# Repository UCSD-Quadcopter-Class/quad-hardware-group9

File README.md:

# CSE 190 - QUAD-HARDWARE

This repo stores all of the files used during the creation of the quadcopter's
hardware design portion of the lab. The main schematic for the quadcopter is
`./quadcopter.sch`. The board file is `./quadcopter.brd`. The CAM files for the
board are in the file `./CAM/Group9-cam.zip`. Routing should be completed and
inspection is in progress.

## What do the Directories Contain?

### `./lbr`

Contains all of the library files used in EAGLE to create the schematic.

### `./datasheets`

Contains all of the datasheets or reference pages for the parts used in the 
quadcopter board.

### `./reference_sch`

Contains the shematics that were used as a reference while creating the 
quadcopter schematic.

### `./design_reviews`

Should contain all of the files that were created during a design review check.

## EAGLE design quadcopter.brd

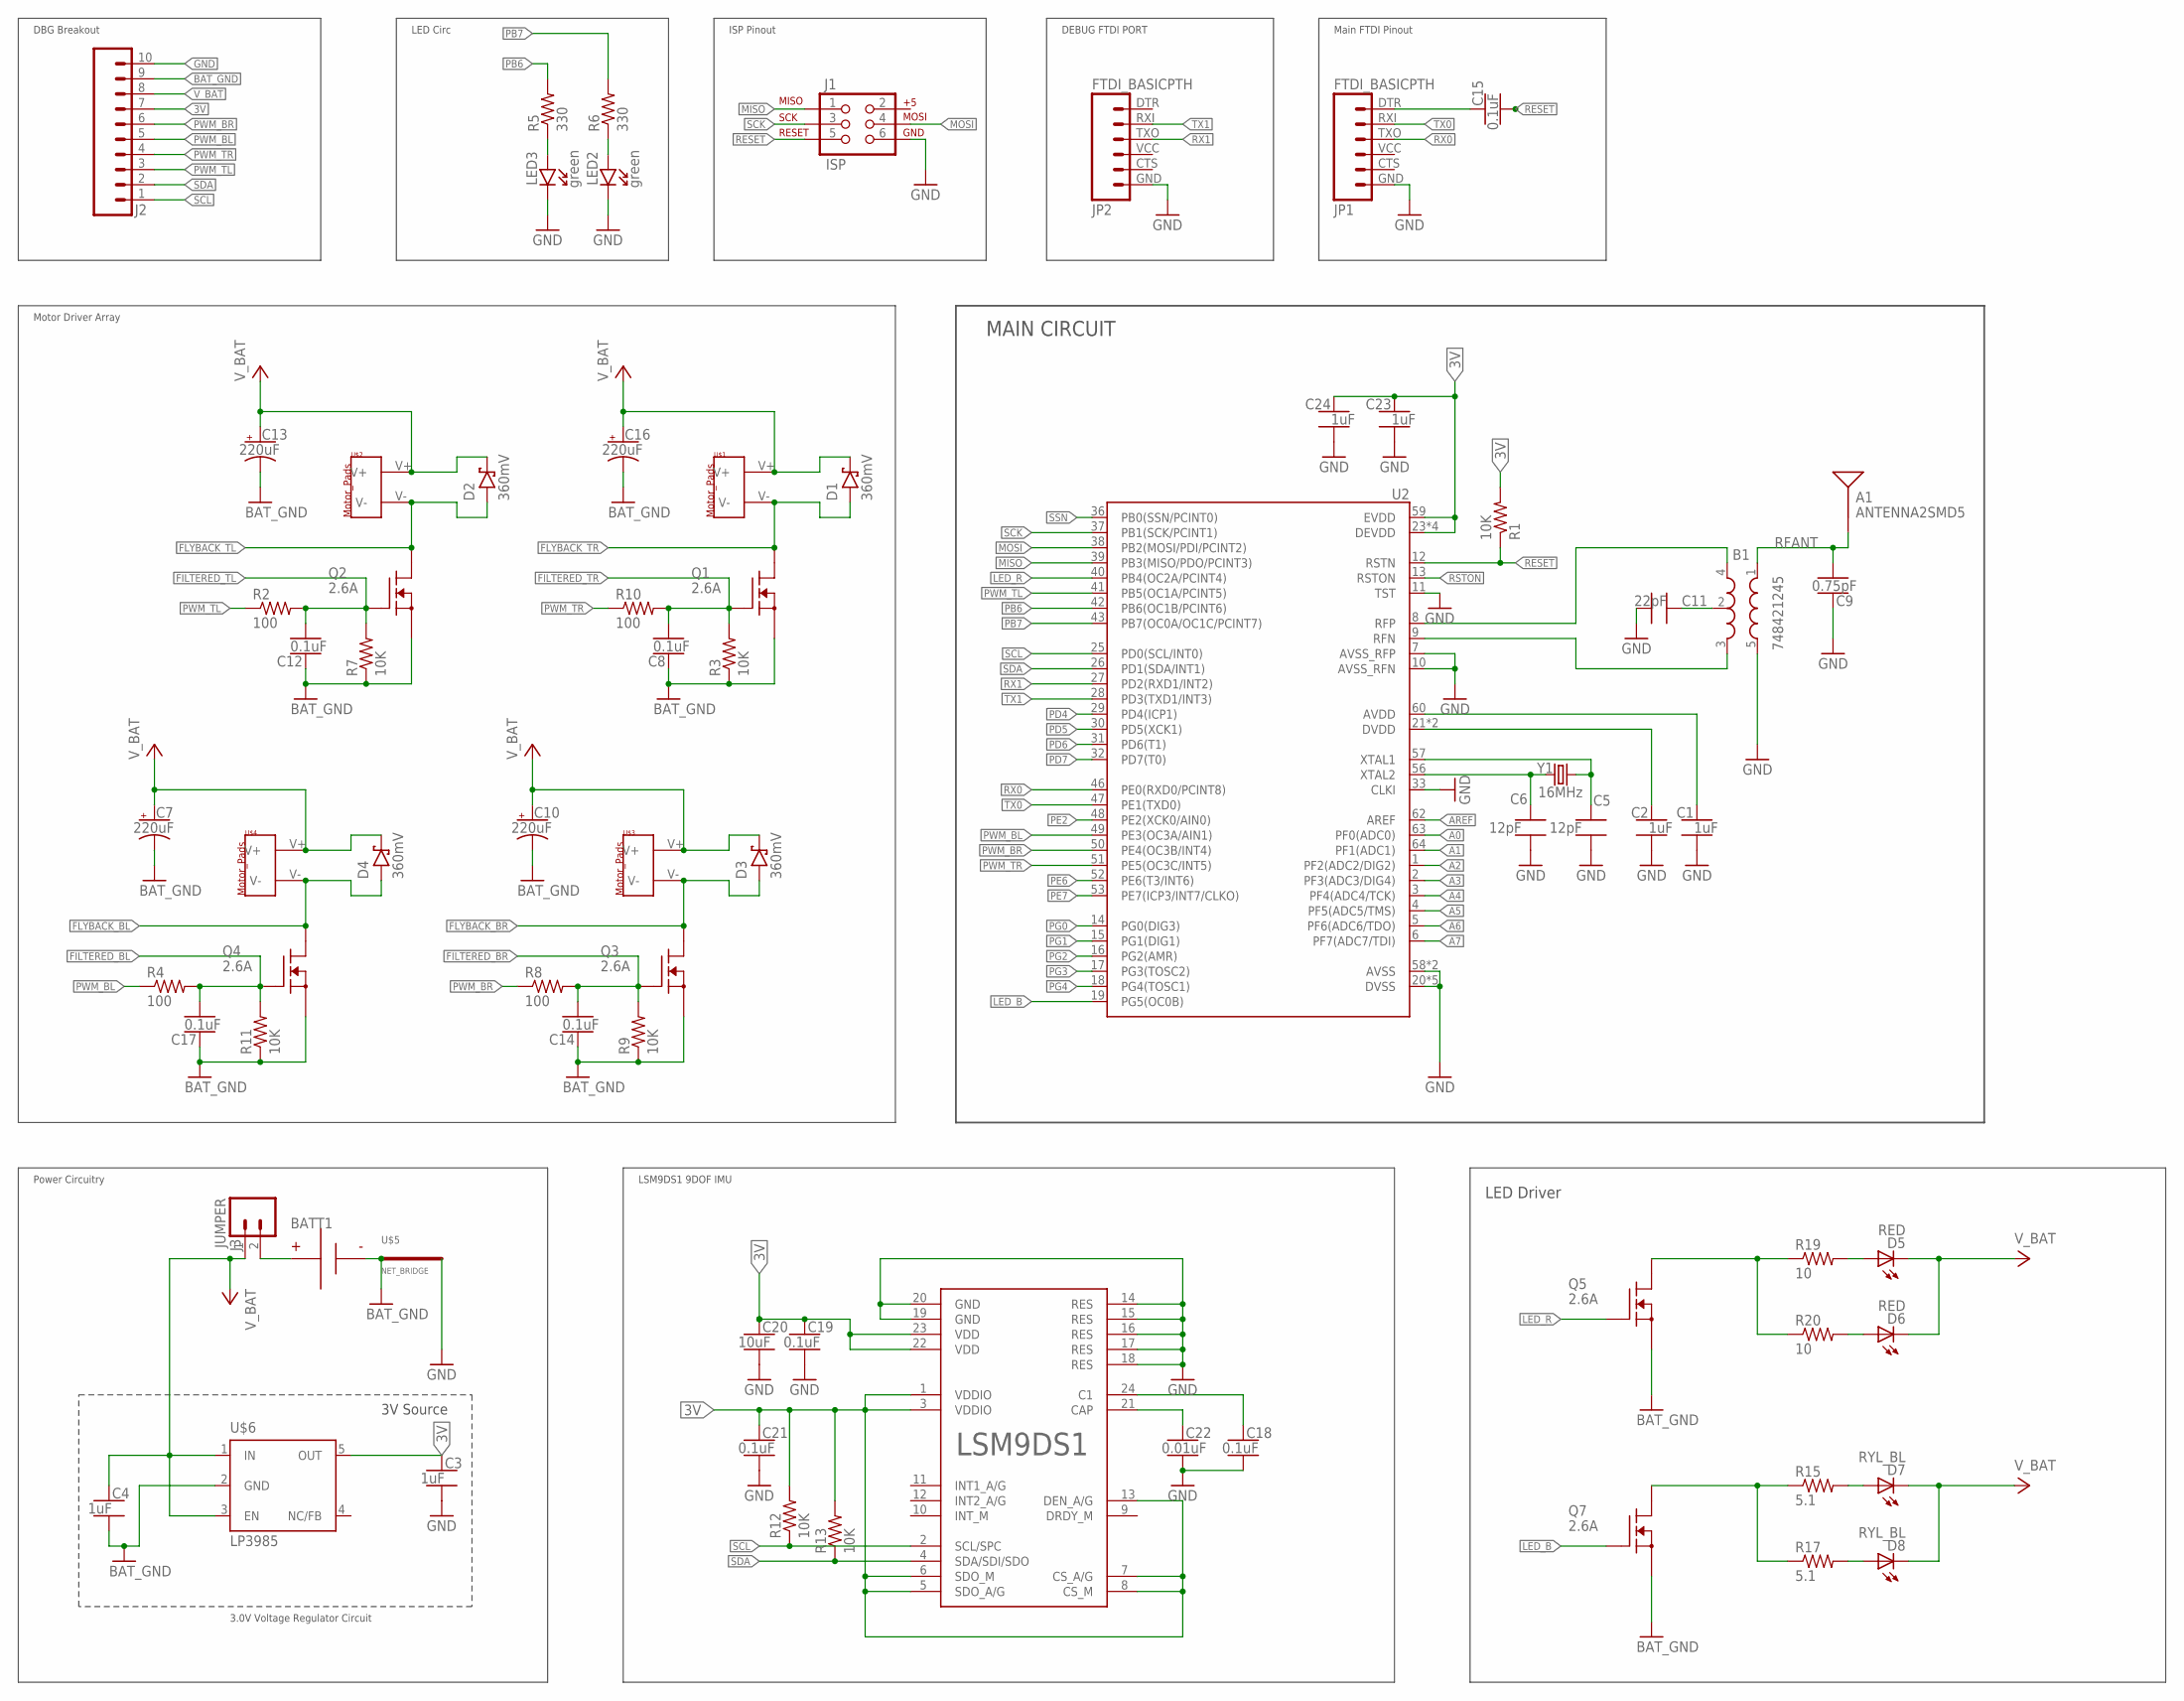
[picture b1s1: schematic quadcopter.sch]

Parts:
A1: ANTENNA2SMD5; ANTENNA-CHIP5
B1: 748421245; BALUN
BATT1: BATTERY-HUBSAN-W/HOLDER; BATTERY-W/HOLDER-380MAH-HUBSAN
C1, C2, C3, C4, C23, C24: 1uF; CAPC2012X140_HS
C5, C6: 12pF; CAPC2012X140_HS
C7, C10, C13, C16: 220uF; CAPMP7343X310_HS
C8, C12, C14, C15, C17, C18, C19, C21: 0.1uF; CAPC2012X140_HS
C9: 0.75pF; CAPC2012X140_HS
C11: 22pF; CAPC2012X140_HS
C20: 10uF; CAPC2012X140_HS
C22: 0.01uF; CAPC2012X140_HS
D1, D2, D3, D4: 360mV; SOD3716X135_HS
D5, D6: RED; XQ-A-1616
D7, D8: RYL_BL; XQ-A-1616
J1: ISP; 2X3-NS
J2: SIP-10_TH-254X10; HDRV10W63P254_10X1_2540X254H838_HS
J3: JUMPER; MALE_HEADER_2X1_0.1IN
JP1, JP2: FTDI_BASICPTH; FTDI_BASIC
LED2, LED3: green; LEDSC125X200X120-2_HS
LSM9DS1: LSM9DS1_IMU; LSM9DS1_LGA24L
Q1, Q2, Q3, Q4, Q5, Q7: 2.6A; SOT-23
R1, R3, R7, R9, R11, R12, R13: 10K; RESC2012X60_HS
R2, R4, R8, R10: 100; RESC2012X60_HS
R5, R6: 330; RESC2012X60_HS
R15, R17: 5.1; PSC_RESIST_805_LR
R19, R20: 10; PSC_RESIST_805
U2: ATMEGA128RFA1; QFN-64
U$1, U$2, U$3, U$4: MOTOR_PADS
U$5: NET_BRIDGE
U$6: LP3985; SOT23-DBV
Y1: 16MHz; CRYSTAL-SMD-5X3

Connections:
3V: C3.1, C19.1, C20.1, C21.1, C23.1, C24.1, J2.7, LSM9DS1.1 (VDDIO), LSM9DS1.3 (VDDIO), LSM9DS1.5 (SDO_A/G), LSM9DS1.6 (SDO_M), LSM9DS1.7 (CS_A/G), LSM9DS1.8 (CS_M), LSM9DS1.13 (DEN_A/G), LSM9DS1.22 (VDD), LSM9DS1.23 (VDD), R1.2, R12.2, R13.2, U2.23 (DEVDD), U2.34 (DEVDD), U2.44 (DEVDD), U2.54 (DEVDD), U2.59 (EVDD), U$6.5 (OUT)
A0: U2.63 (PF0(ADC0))
A1: U2.64 (PF1(ADC1))
A2: U2.1 (PF2(ADC2/DIG2))
A3: U2.2 (PF3(ADC3/DIG4))
A4: U2.3 (PF4(ADC4/TCK))
A5: U2.4 (PF5(ADC5/TMS))
A6: U2.5 (PF6(ADC6/TDO))
A7: U2.6 (PF7(ADC7/TDI))
AREF: U2.62 (AREF)
AVDD: C1.1, U2.60 (AVDD)
BAT_GND: BATT1.- (N), C4.2, C7.2 (-), C8.1, C10.2 (-), C12.1, C13.2 (-), C14.1, C16.2 (-), C17.1, J2.9, Q1.S, Q2.S, Q3.S, Q4.S, Q5.S, Q7.S, R3.1, R7.1, R9.1, R11.1, U$5.P$1, U$6.2 (GND)
DTR: C15.1, JP1.DTR (1)
DVDD: C2.1, U2.21 (DVDD), U2.22 (DVDD)
FILTERED_BL: C17.2, Q4.G, R4.2, R11.2
FILTERED_BR: C14.2, Q3.G, R8.2, R9.2
FILTERED_TL: C12.2, Q2.G, R2.2, R7.2
FILTERED_TR: C8.2, Q1.G, R3.2, R10.2
FLYBACK_BL: D4.A, Q4.D, U$4.V-
FLYBACK_BR: D3.A, Q3.D, U$3.V-
FLYBACK_TL: D2.A, Q2.D, U$2.V-
FLYBACK_TR: D1.A, Q1.D, U$1.V-
GND: B1.5 (GND), C1.2, C2.2, C3.2, C5.2, C6.2, C9.1, C11.2, C18.2, C19.2, C20.2, C21.2, C22.2, C23.2, C24.2, J1.6, J2.10, JP1.GND (6), JP2.GND (6), LED2.C, LED3.C, LSM9DS1.14 (RES), LSM9DS1.15 (RES), LSM9DS1.16 (RES), LSM9DS1.17 (RES), LSM9DS1.18 (RES), LSM9DS1.19 (GND), LSM9DS1.20 (GND), U2.7 (AVSS_RFP), U2.10 (AVSS_RFN), U2.11 (TST), U2.20 (DVSS), U2.24 (DVSS), U2.33 (CLKI), U2.35 (DVSS), U2.45 (DVSS), U2.55 (DVSS), U2.58 (AVSS), U2.61 (AVSS), U$5.P$2
LED_B: Q7.G, U2.19 (PG5(OC0B))
LED_R: Q5.G, U2.40 (PB4(OC2A/PCINT4))
MISO: J1.1, U2.39 (PB3(MISO/PDO/PCINT3))
MOSI: J1.4, U2.38 (PB2(MOSI/PDI/PCINT2))
unnamed: BATT1.+, J3.2
unnamed: C5.1, U2.57 (XTAL1), Y1.3 (2)
unnamed: C6.1, U2.56 (XTAL2), Y1.1
unnamed: C18.1, LSM9DS1.24 (C1)
unnamed: Q5.D, R19.P$1 (1), R20.P$1 (1)
unnamed: B1.2 (GND), C11.1
unnamed: LED3.A, R5.1
unnamed: C22.1, LSM9DS1.21 (CAP)
unnamed: Q7.D, R15.P$1 (1), R17.P$1 (1)
unnamed: D5.A, R19.P$2 (2)
unnamed: D6.A, R20.P$2 (2)
unnamed: LED2.A, R6.1
unnamed: D7.A, R15.P$2 (2)
unnamed: D8.A, R17.P$2 (2)
PB6: R5.2, U2.42 (PB6(OC1B/PCINT6))
PB7: R6.2, U2.43 (PB7(OC0A/OC1C/PCINT7))
PD4: U2.29 (PD4(ICP1))
PD5: U2.30 (PD5(XCK1))
PD6: U2.31 (PD6(T1))
PD7: U2.32 (PD7(T0))
PE2: U2.48 (PE2(XCK0/AIN0))
PE6: U2.52 (PE6(T3/INT6))
PE7: U2.53 (PE7(ICP3/INT7/CLKO))
PG0: U2.14 (PG0(DIG3))
PG1: U2.15 (PG1(DIG1))
PG2: U2.16 (PG2(AMR))
PG3: U2.17 (PG3(TOSC2))
PG4: U2.18 (PG4(TOSC1))
PWM_BL: J2.5, R4.1, U2.49 (PE3(OC3A/AIN1))
PWM_BR: J2.6, R8.1, U2.50 (PE4(OC3B/INT4))
PWM_TL: J2.3, R2.1, U2.41 (PB5(OC1A/PCINT5))
PWM_TR: J2.4, R10.1, U2.51 (PE5(OC3C/INT5))
RESET: C15.2, J1.5, R1.1, U2.12 (RSTN)
RFANT: A1.FEED, B1.1 (IN), C9.2
RFN: B1.3 (OUT2), U2.9 (RFN)
RFP: B1.4 (OUT1), U2.8 (RFP)
RSTON: U2.13 (RSTON)
RX0: JP1.TXO (3), U2.46 (PE0(RXD0/PCINT8))
RX1: JP2.TXO (3), U2.27 (PD2(RXD1/INT2))
SCK: J1.3, U2.37 (PB1(SCK/PCINT1))
SCL: J2.1, LSM9DS1.2 (SCL/SPC), R12.1, U2.25 (PD0(SCL/INT0))
SDA: J2.2, LSM9DS1.4 (SDA/SDI/SDO), R13.1, U2.26 (PD1(SDA/INT1))
SSN: U2.36 (PB0(SSN/PCINT0))
TX0: JP1.RXI (2), U2.47 (PE1(TXD0))
TX1: JP2.RXI (2), U2.28 (PD3(TXD1/INT3))
V_BAT: C4.1, C7.1 (+), C10.1 (+), C13.1 (+), C16.1 (+), D1.C, D2.C, D3.C, D4.C, D5.C, D6.C, D7.C, D8.C, J2.8, J3.1, U$1.V+, U$2.V+, U$3.V+, U$4.V+, U$6.1 (IN), U$6.3 (EN)

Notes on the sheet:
DEBUG FTDI PORT
ISP Pinout
Main FTDI Pinout
LED Circ
Motor Driver Array
DBG Breakout
Power Circuitry
3.0V Voltage Regulator Circuit
LSM9DS1 9DOF IMU
MAIN CIRCUIT
LED Driver
3V Source

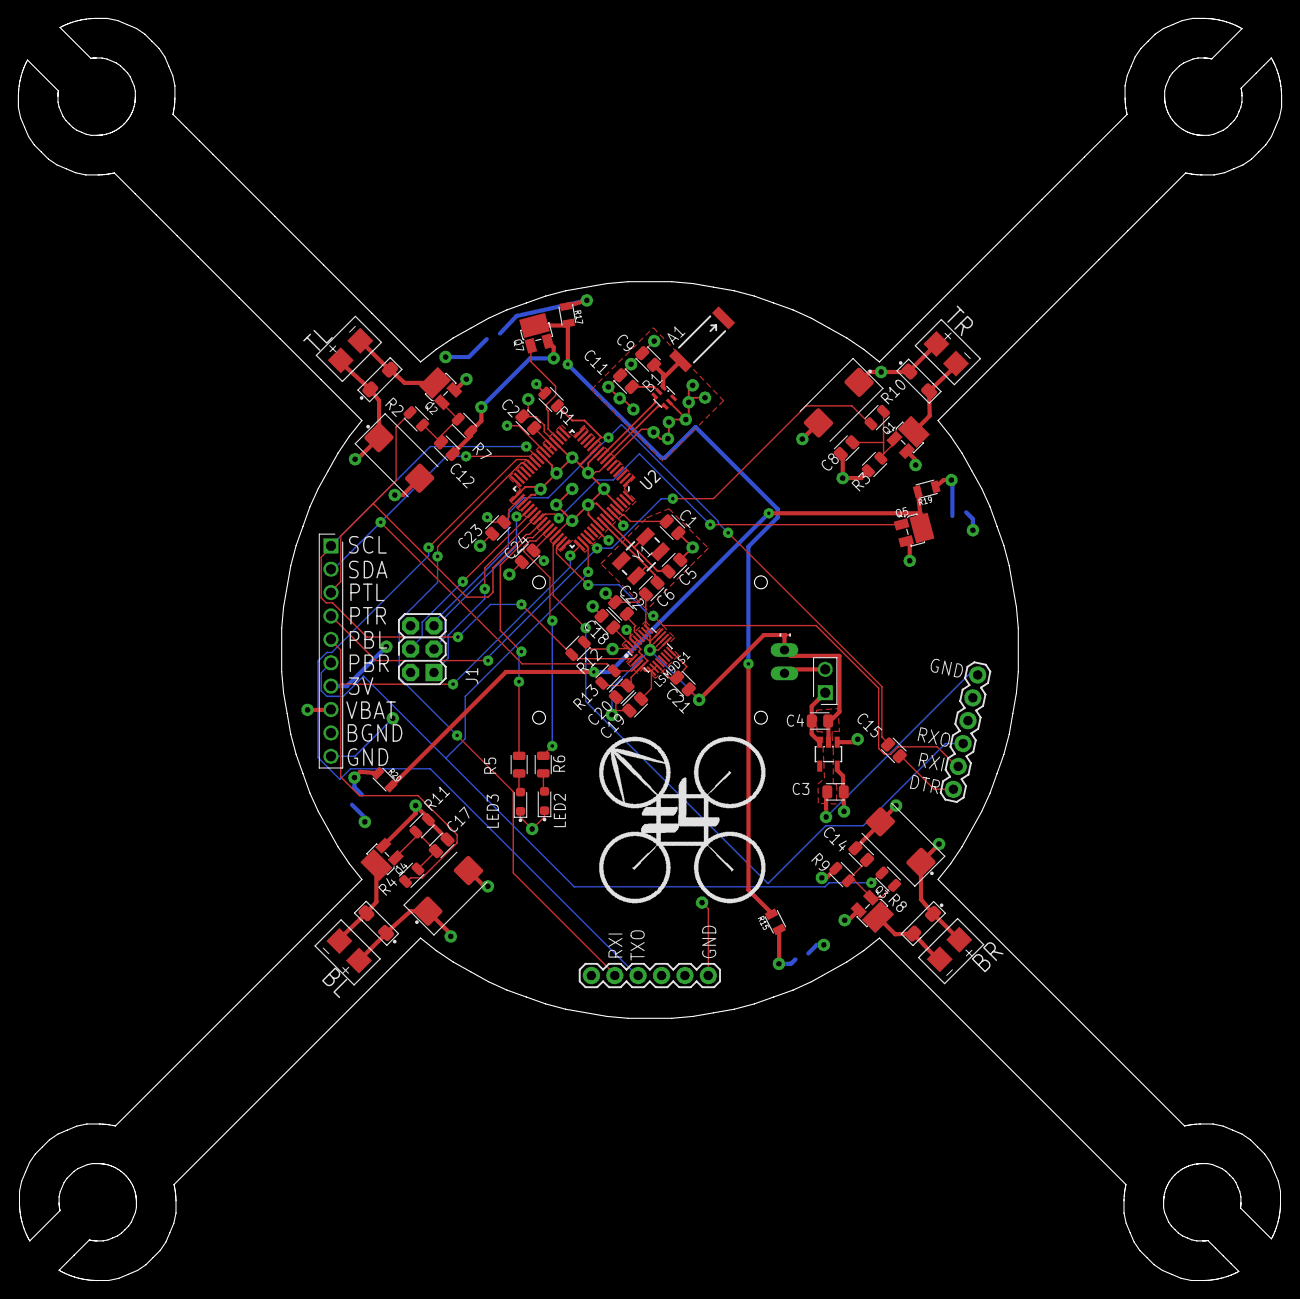
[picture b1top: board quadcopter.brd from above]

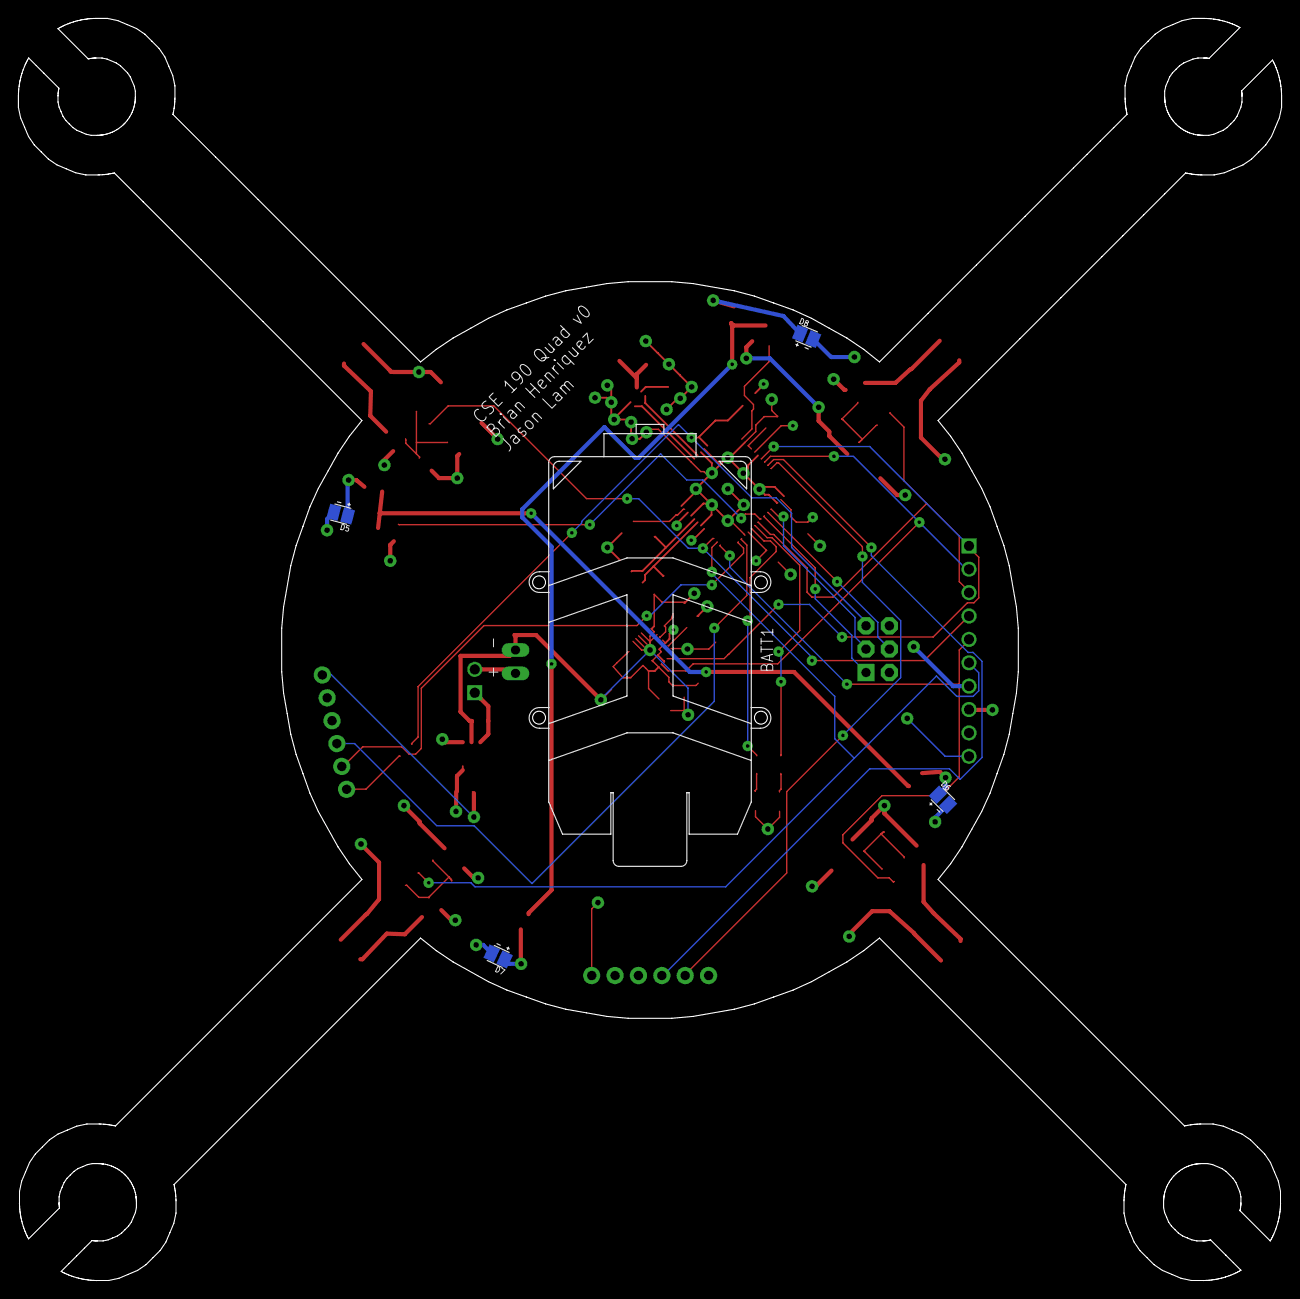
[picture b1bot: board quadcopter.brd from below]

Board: 4 copper layers, 137.2 x 137.1 mm, 75 parts (5 on the bottom side), 50 nets.

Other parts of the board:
U$7: LOGO_QUAD

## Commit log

2017-04-20 Push initial schematic and documentation
2017-04-20 updated whoami
2017-04-22 Fixed a few errors. Revised schematic and docs for new LEDs
2017-04-22 Forgot to commit libraries. Fixed a few errors found on Eagle LINT.
2017-04-24 Fixed jumper placement and PWM pin input.
2017-04-25 Commit design reviews and performed revisions requested.
2017-04-26 Changed schematic slightly. Created basic board layout.
2017-04-26 Moved silkscreen for legibility. Added labels and orientation reference.
2017-04-27 instructior review of original schematic
2017-05-01 Corrected mistakes found on schematics and libraries. Rerouted board from updated schematic.
2017-05-02 Added a logo to the board. Updated libary with logo.
2017-05-05 Forgot to add board design reviews.
2017-05-11 Finished new routing & added cam zip
2017-05-11 Fixed directory structure
2017-05-11 swanson review
2017-05-14 more schematic comments from swanson
2017-05-15 Updated board and cam to meet new board review changes.
2017-05-16 Completed board routing
